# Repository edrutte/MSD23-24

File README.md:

# MSD 23-24 18661 Autonomous Chess Board
## Team Members

* [Evan Ruttenberg](https://github.com/edrutte) - System Engineer
* [Alec Paul](https://github.com/asp6244) - Project Manager
* Nick Larrabee - Purchasing Agent
* Devin Alberto - Facilitator
* [Justin Chienyuen](https://github.com/jcc3249) - Team Communicator

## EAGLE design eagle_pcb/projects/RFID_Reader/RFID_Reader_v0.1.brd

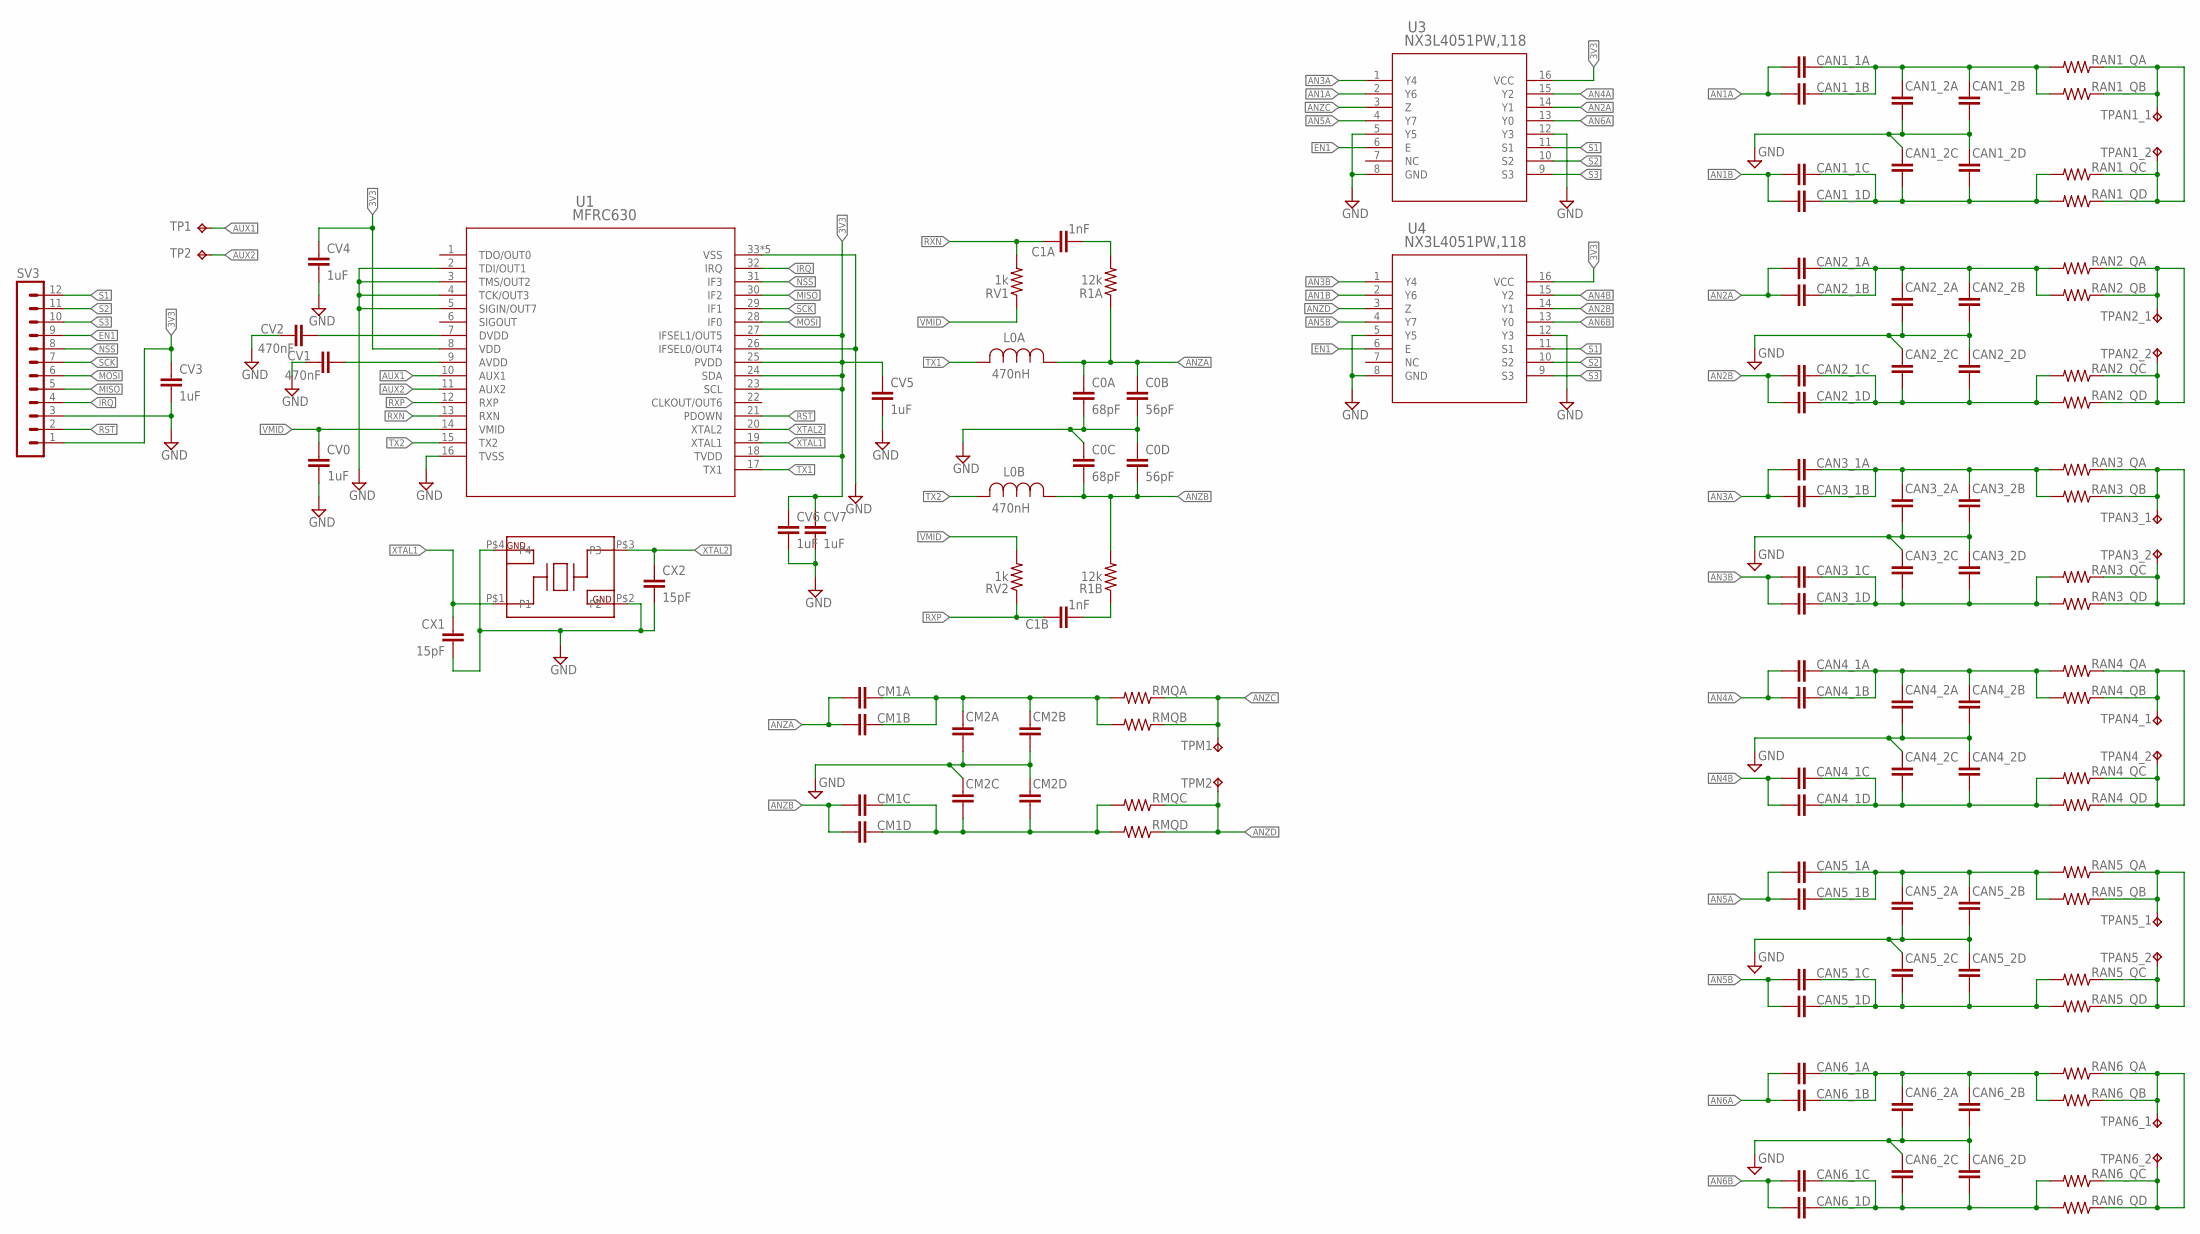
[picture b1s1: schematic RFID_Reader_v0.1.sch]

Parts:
C0A, C0C: 68pF; C0805
C0B, C0D: 56pF; C0805
C1A, C1B: 1nF; C0805
CAN1_1A, CAN1_1B, CAN1_1C, CAN1_1D, CAN1_2A, CAN1_2B, CAN1_2C, CAN1_2D, CAN2_1A, CAN2_1B, CAN2_1C, CAN2_1D, CAN2_2A, CAN2_2B, CAN2_2C, CAN2_2D, CAN3_1A, CAN3_1B, CAN3_1C, CAN3_1D, CAN3_2A, CAN3_2B, CAN3_2C, CAN3_2D, CAN4_1A, CAN4_1B, CAN4_1C, CAN4_1D, CAN4_2A, CAN4_2B, CAN4_2C, CAN4_2D, CAN5_1A, CAN5_1B, CAN5_1C, CAN5_1D, CAN5_2A, CAN5_2B, CAN5_2C, CAN5_2D, CAN6_1A, CAN6_1B, CAN6_1C, CAN6_1D, CAN6_2A, CAN6_2B, CAN6_2C, CAN6_2D: C-EUC0805; C0805
CM1A, CM1B, CM1C, CM1D, CM2A, CM2B, CM2C, CM2D: C-EUC0805; C0805
CV0, CV3, CV4, CV5, CV6, CV7: 1uF; C0402
CV1, CV2: 470nF; C0402
CX1, CX2: 15pF; C0402
L0A, L0B: 470nH; IND_BOURNS_CE201210_C
R1A, R1B: 12k; R0805
RAN1_QA, RAN1_QB, RAN1_QC, RAN1_QD, RAN2_QA, RAN2_QB, RAN2_QC, RAN2_QD, RAN3_QA, RAN3_QB, RAN3_QC, RAN3_QD, RAN4_QA, RAN4_QB, RAN4_QC, RAN4_QD, RAN5_QA, RAN5_QB, RAN5_QC, RAN5_QD, RAN6_QA, RAN6_QB, RAN6_QC, RAN6_QD: R-US_R0805; R0805
RMQA: R-US_R0805; R0805
RMQB: R-US_R0805; R0805
RMQC: R-US_R0805; R0805
RMQD: R-US_R0805; R0805
RV1, RV2: 1k; R0805
SV3: MA12-1
TP1, TP2: TPTP10R; TP10R
TPAN1_1, TPAN1_2, TPAN2_1, TPAN2_2, TPAN3_1, TPAN3_2, TPAN4_1, TPAN4_2, TPAN5_1, TPAN5_2, TPAN6_1, TPAN6_2: TPTP10R; TP10R
TPM1, TPM2: TPTP10R; TP10R
U1: MFRC630; HVQFN32_SOT617-1_NXP-M
U2: E3SB27; DFN320X250X75-4N
U3, U4: NX3L4051PW,118; TSSOP16_NXP-M

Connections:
3V3: CV3.1, CV4.1, CV5.1, CV6.1, CV7.1, SV3.1, U1.8 (VDD), U1.18 (TVDD), U1.23 (SCL), U1.24 (SDA), U1.25 (PVDD), U1.27 (IFSEL1/OUT5), U3.16 (VCC), U4.16 (VCC)
AN1A: CAN1_1A.2, CAN1_1B.2, U3.2 (Y6)
AN1B: CAN1_1C.2, CAN1_1D.2, U4.2 (Y6)
AN2A: CAN2_1A.2, CAN2_1B.2, U3.14 (Y1)
AN2B: CAN2_1C.2, CAN2_1D.2, U4.14 (Y1)
AN3A: CAN3_1A.2, CAN3_1B.2, U3.1 (Y4)
AN3B: CAN3_1C.2, CAN3_1D.2, U4.1 (Y4)
AN4A: CAN4_1A.2, CAN4_1B.2, U3.15 (Y2)
AN4B: CAN4_1C.2, CAN4_1D.2, U4.15 (Y2)
AN5A: CAN5_1A.2, CAN5_1B.2, U3.4 (Y7)
AN5B: CAN5_1C.2, CAN5_1D.2, U4.4 (Y7)
AN6A: CAN6_1A.2, CAN6_1B.2, U3.13 (Y0)
AN6B: CAN6_1C.2, CAN6_1D.2, U4.13 (Y0)
ANZA: C0A.1, C0B.1, CM1A.2, CM1B.2, L0A.1, R1A.1
ANZB: C0C.2, C0D.2, CM1C.2, CM1D.2, L0B.1, R1B.2
ANZC: RMQA.1, RMQB.1, TPM1.TP, U3.3 (Z)
ANZD: RMQC.1, RMQD.1, TPM2.TP, U4.3 (Z)
AUX1: TP1.TP, U1.10 (AUX1)
AUX2: TP2.TP, U1.11 (AUX2)
EN1: SV3.9, U3.6 (E), U4.6 (E)
GND: C0A.2, C0B.2, C0C.1, C0D.1, CAN1_2A.2, CAN1_2B.2, CAN1_2C.1, CAN1_2D.1, CAN2_2A.2, CAN2_2B.2, CAN2_2C.1, CAN2_2D.1, CAN3_2A.2, CAN3_2B.2, CAN3_2C.1, CAN3_2D.1, CAN4_2A.2, CAN4_2B.2, CAN4_2C.1, CAN4_2D.1, CAN5_2A.2, CAN5_2B.2, CAN5_2C.1, CAN5_2D.1, CAN6_2A.2, CAN6_2B.2, CAN6_2C.1, CAN6_2D.1, CM2A.2, CM2B.2, CM2C.1, CM2D.1, CV0.2, CV1.2, CV2.2, CV3.2, CV4.2, CV5.2, CV6.2, CV7.2, CX1.2, CX2.2, SV3.3, U1.2 (TDI/OUT1), U1.3 (TMS/OUT2), U1.4 (TCK/OUT3), U1.5 (SIGIN/OUT7), U1.16 (TVSS), U1.26 (IFSEL0/OUT4), U1.33 (VSS), U1.P$1 (VSS), U1.P$2 (VSS), U1.P$3 (VSS), U1.P$4 (VSS), U2.P$2 (P2), U2.P$4 (P4), U3.5 (Y5), U3.8 (GND), U3.12 (Y3), U4.5 (Y5), U4.8 (GND), U4.12 (Y3)
IRQ: SV3.4, U1.32 (IRQ)
MISO: SV3.5, U1.30 (IF2)
MOSI: SV3.6, U1.28 (IF0)
unnamed: CM1C.1, CM1D.1, CM2C.2, CM2D.2, RMQC.2, RMQD.2
unnamed: C1A.2, R1A.2
unnamed: CM1A.1, CM1B.1, CM2A.1, CM2B.1, RMQA.2, RMQB.2
unnamed: CAN2_1C.1, CAN2_1D.1, CAN2_2C.2, CAN2_2D.2, RAN2_QC.2, RAN2_QD.2
unnamed: CAN2_1A.1, CAN2_1B.1, CAN2_2A.1, CAN2_2B.1, RAN2_QA.2, RAN2_QB.2
unnamed: RAN2_QA.1, RAN2_QB.1, RAN2_QC.1, RAN2_QD.1, TPAN2_1.TP, TPAN2_2.TP
unnamed: CAN1_1C.1, CAN1_1D.1, CAN1_2C.2, CAN1_2D.2, RAN1_QC.2, RAN1_QD.2
unnamed: CAN1_1A.1, CAN1_1B.1, CAN1_2A.1, CAN1_2B.1, RAN1_QA.2, RAN1_QB.2
unnamed: RAN1_QA.1, RAN1_QB.1, RAN1_QC.1, RAN1_QD.1, TPAN1_1.TP, TPAN1_2.TP
unnamed: CAN3_1C.1, CAN3_1D.1, CAN3_2C.2, CAN3_2D.2, RAN3_QC.2, RAN3_QD.2
unnamed: CAN3_1A.1, CAN3_1B.1, CAN3_2A.1, CAN3_2B.1, RAN3_QA.2, RAN3_QB.2
unnamed: RAN3_QA.1, RAN3_QB.1, RAN3_QC.1, RAN3_QD.1, TPAN3_1.TP, TPAN3_2.TP
unnamed: CAN4_1C.1, CAN4_1D.1, CAN4_2C.2, CAN4_2D.2, RAN4_QC.2, RAN4_QD.2
unnamed: CAN4_1A.1, CAN4_1B.1, CAN4_2A.1, CAN4_2B.1, RAN4_QA.2, RAN4_QB.2
unnamed: RAN4_QA.1, RAN4_QB.1, RAN4_QC.1, RAN4_QD.1, TPAN4_1.TP, TPAN4_2.TP
unnamed: CAN5_1C.1, CAN5_1D.1, CAN5_2C.2, CAN5_2D.2, RAN5_QC.2, RAN5_QD.2
unnamed: CAN5_1A.1, CAN5_1B.1, CAN5_2A.1, CAN5_2B.1, RAN5_QA.2, RAN5_QB.2
unnamed: C1B.2, R1B.1
unnamed: RAN5_QA.1, RAN5_QB.1, RAN5_QC.1, RAN5_QD.1, TPAN5_1.TP, TPAN5_2.TP
unnamed: CAN6_1C.1, CAN6_1D.1, CAN6_2C.2, CAN6_2D.2, RAN6_QC.2, RAN6_QD.2
unnamed: CAN6_1A.1, CAN6_1B.1, CAN6_2A.1, CAN6_2B.1, RAN6_QA.2, RAN6_QB.2
unnamed: RAN6_QA.1, RAN6_QB.1, RAN6_QC.1, RAN6_QD.1, TPAN6_1.TP, TPAN6_2.TP
unnamed: CV2.1, U1.7 (DVDD)
unnamed: CV1.1, U1.9 (AVDD)
NSS: SV3.8, U1.31 (IF3)
RST: SV3.2, U1.21 (PDOWN)
RXN: C1A.1, RV1.2, U1.13 (RXN)
RXP: C1B.1, RV2.1, U1.12 (RXP)
S1: SV3.12, U3.11 (S1), U4.11 (S1)
S2: SV3.11, U3.10 (S2), U4.10 (S2)
S3: SV3.10, U3.9 (S3), U4.9 (S3)
SCK: SV3.7, U1.29 (IF1)
TX1: L0A.2, U1.17 (TX1)
TX2: L0B.2, U1.15 (TX2)
VMID: CV0.1, RV1.1, RV2.2, U1.14 (VMID)
XTAL1: CX1.1, U1.19 (XTAL1), U2.P$1 (P1)
XTAL2: CX2.1, U1.20 (XTAL2), U2.P$3 (P3)

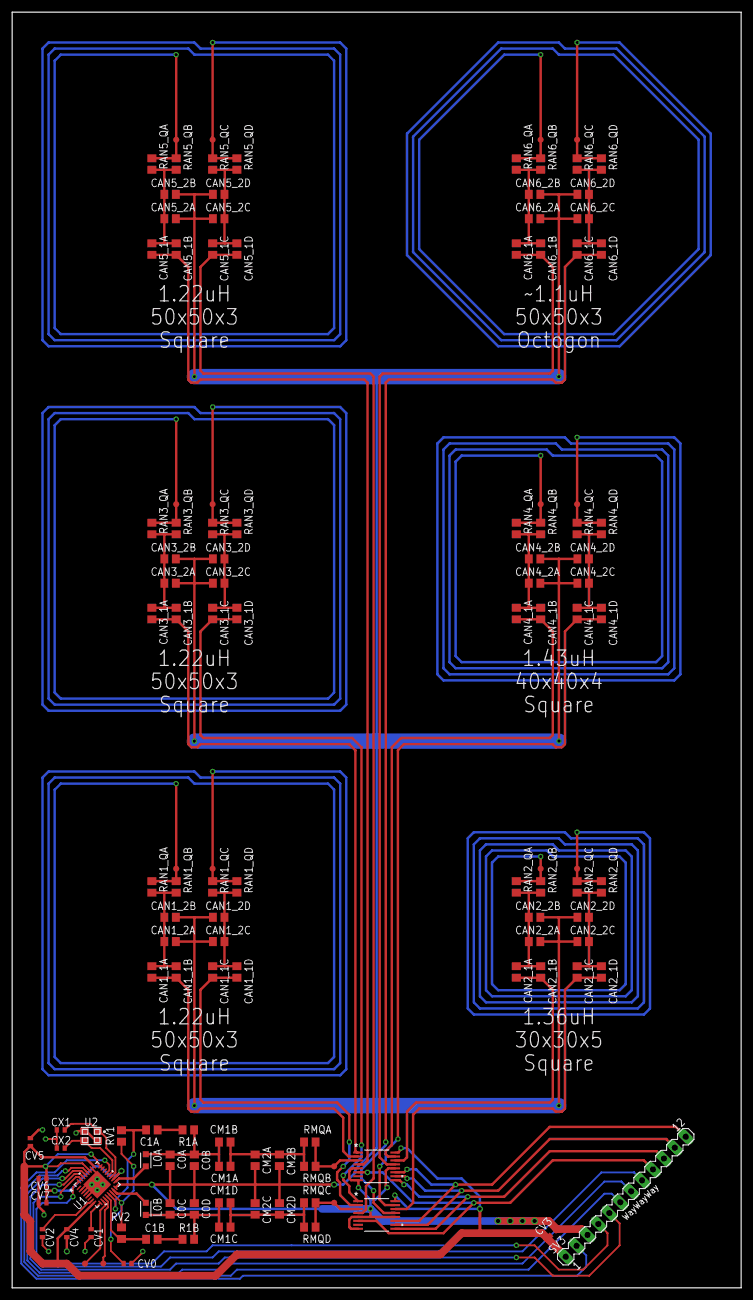
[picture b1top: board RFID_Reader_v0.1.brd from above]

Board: 2 copper layers, 120.0 x 210.0 mm, 127 parts (0 on the bottom side), 61 nets.

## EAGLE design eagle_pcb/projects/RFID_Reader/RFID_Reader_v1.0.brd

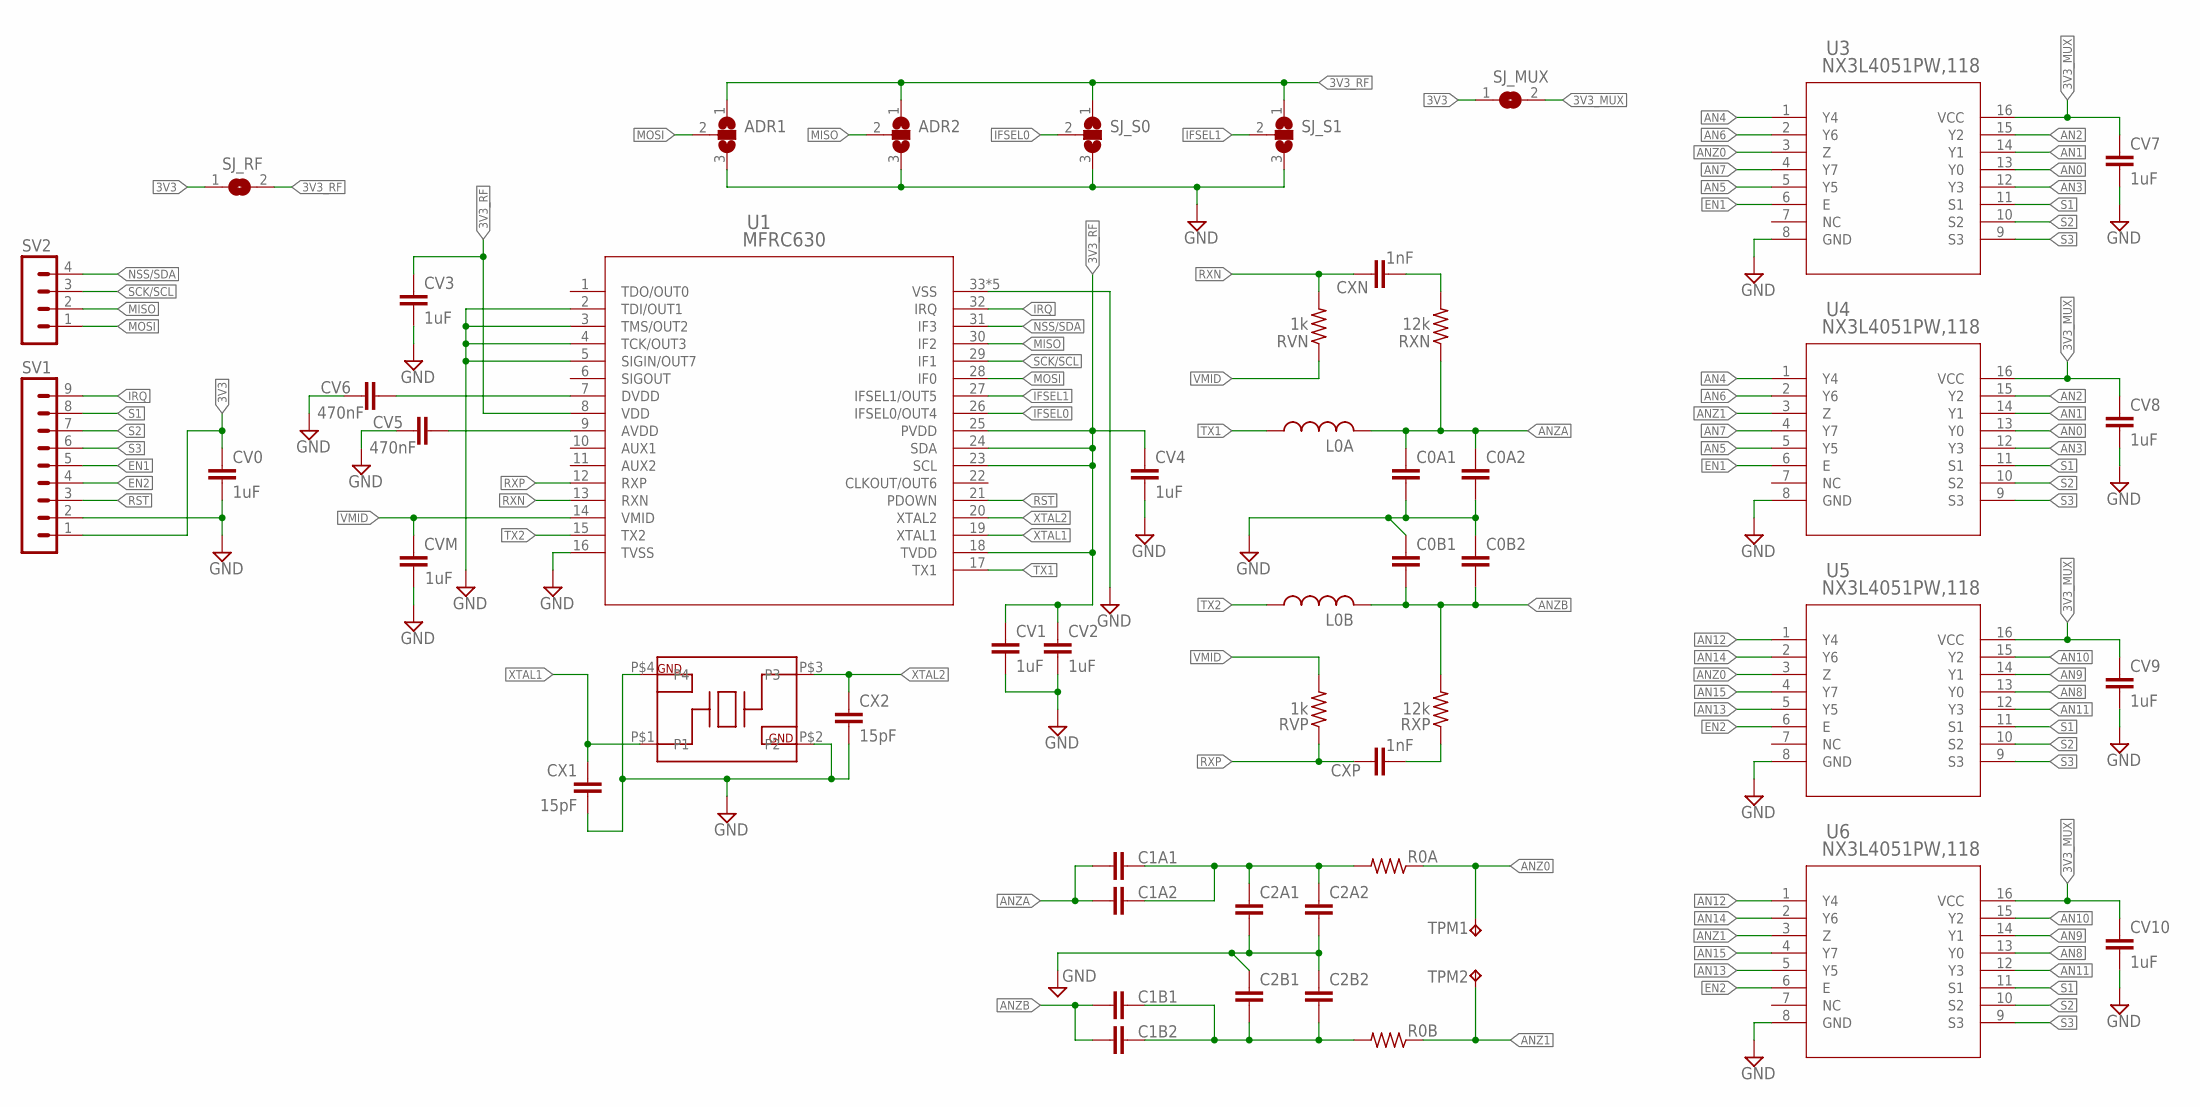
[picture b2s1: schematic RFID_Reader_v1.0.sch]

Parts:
ADR1, ADR2: SJ2W; SJ_2
C0A1, C0A2, C0B1, C0B2, C1A1, C1A2, C1B1, C1B2, C2A1, C2A2, C2B1, C2B2: C-EUC0805; C0805
CV0, CV1, CV2, CV3, CV4, CV7, CV8, CV9, CV10: 1uF; C0402
CV5, CV6: 470nF; C0402
CVM: 1uF; C0402
CX1, CX2: 15pF; C0402
CXN: 1nF; C0805
CXP: 1nF; C0805
L0A, L0B: L0806
R0A, R0B: R-US_R0805; R0805
RVN: 1k; R0805
RVP: 1k; R0805
RXN: 12k; R0805
RXP: 12k; R0805
SJ_MUX: SJ
SJ_RF: SJ
SJ_S0, SJ_S1: SJ2W; SJ_2
SV1: MA09-1
SV2: MA04-1
TPM1, TPM2: TPTP10R; TP10R
U1: MFRC630; HVQFN32_SOT617-1_NXP-M
U2: E3SB27; DFN320X250X75-4N
U3, U4, U5, U6: NX3L4051PW,118; TSSOP16_NXP-M

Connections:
3V3: CV0.1, SJ_MUX.1, SJ_RF.1, SV1.1
3V3_MUX: CV7.1, CV8.1, CV9.1, CV10.1, SJ_MUX.2, U3.16 (VCC), U4.16 (VCC), U5.16 (VCC), U6.16 (VCC)
3V3_RF: ADR1.1, ADR2.1, CV1.1, CV2.1, CV3.1, CV4.1, SJ_RF.2, SJ_S0.1, SJ_S1.1, U1.8 (VDD), U1.18 (TVDD), U1.23 (SCL), U1.24 (SDA), U1.25 (PVDD)
AN0: U3.13 (Y0), U4.13 (Y0)
AN1: U3.14 (Y1), U4.14 (Y1)
AN2: U3.15 (Y2), U4.15 (Y2)
AN3: U3.12 (Y3), U4.12 (Y3)
AN4: U3.1 (Y4), U4.1 (Y4)
AN5: U3.5 (Y5), U4.5 (Y5)
AN6: U3.2 (Y6), U4.2 (Y6)
AN7: U3.4 (Y7), U4.4 (Y7)
AN8: U5.13 (Y0), U6.13 (Y0)
AN9: U5.14 (Y1), U6.14 (Y1)
AN10: U5.15 (Y2), U6.15 (Y2)
AN11: U5.12 (Y3), U6.12 (Y3)
AN12: U5.1 (Y4), U6.1 (Y4)
AN13: U5.5 (Y5), U6.5 (Y5)
AN14: U5.2 (Y6), U6.2 (Y6)
AN15: U5.4 (Y7), U6.4 (Y7)
ANZ0: R0A.1, TPM1.TP, U3.3 (Z), U5.3 (Z)
ANZ1: R0B.1, TPM2.TP, U4.3 (Z), U6.3 (Z)
ANZA: C0A1.1, C0A2.1, C1A1.2, C1A2.2, L0A.2, RXN.1
ANZB: C0B1.2, C0B2.2, C1B1.2, C1B2.2, L0B.2, RXP.2
EN1: SV1.5, U3.6 (E), U4.6 (E)
EN2: SV1.4, U5.6 (E), U6.6 (E)
GND: ADR1.3, ADR2.3, C0A1.2, C0A2.2, C0B1.1, C0B2.1, C2A1.2, C2A2.2, C2B1.1, C2B2.1, CV0.2, CV1.2, CV2.2, CV3.2, CV4.2, CV5.2, CV6.2, CV7.2, CV8.2, CV9.2, CV10.2, CVM.2, CX1.2, CX2.2, SJ_S0.3, SJ_S1.3, SV1.2, U1.2 (TDI/OUT1), U1.3 (TMS/OUT2), U1.4 (TCK/OUT3), U1.5 (SIGIN/OUT7), U1.16 (TVSS), U1.33 (VSS), U1.P$1 (VSS), U1.P$2 (VSS), U1.P$3 (VSS), U1.P$4 (VSS), U2.P$2 (P2), U2.P$4 (P4), U3.8 (GND), U4.8 (GND), U5.8 (GND), U6.8 (GND)
IFSEL0: SJ_S0.2, U1.26 (IFSEL0/OUT4)
IFSEL1: SJ_S1.2, U1.27 (IFSEL1/OUT5)
IRQ: SV1.9, U1.32 (IRQ)
MISO: ADR2.2, SV2.2, U1.30 (IF2)
MOSI: ADR1.2, SV2.1, U1.28 (IF0)
unnamed: C1B1.1, C1B2.1, C2B1.2, C2B2.2, R0B.2
unnamed: CXN.2, RXN.2
unnamed: C1A1.1, C1A2.1, C2A1.1, C2A2.1, R0A.2
unnamed: CXP.2, RXP.1
unnamed: CV6.1, U1.7 (DVDD)
unnamed: CV5.1, U1.9 (AVDD)
NSS/SDA: SV2.4, U1.31 (IF3)
RST: SV1.3, U1.21 (PDOWN)
RXN: CXN.1, RVN.2, U1.13 (RXN)
RXP: CXP.1, RVP.1, U1.12 (RXP)
S1: SV1.8, U3.11 (S1), U4.11 (S1), U5.11 (S1), U6.11 (S1)
S2: SV1.7, U3.10 (S2), U4.10 (S2), U5.10 (S2), U6.10 (S2)
S3: SV1.6, U3.9 (S3), U4.9 (S3), U5.9 (S3), U6.9 (S3)
SCK/SCL: SV2.3, U1.29 (IF1)
TX1: L0A.1, U1.17 (TX1)
TX2: L0B.1, U1.15 (TX2)
VMID: CVM.1, RVN.1, RVP.2, U1.14 (VMID)
XTAL1: CX1.1, U1.19 (XTAL1), U2.P$1 (P1)
XTAL2: CX2.1, U1.20 (XTAL2), U2.P$3 (P3)

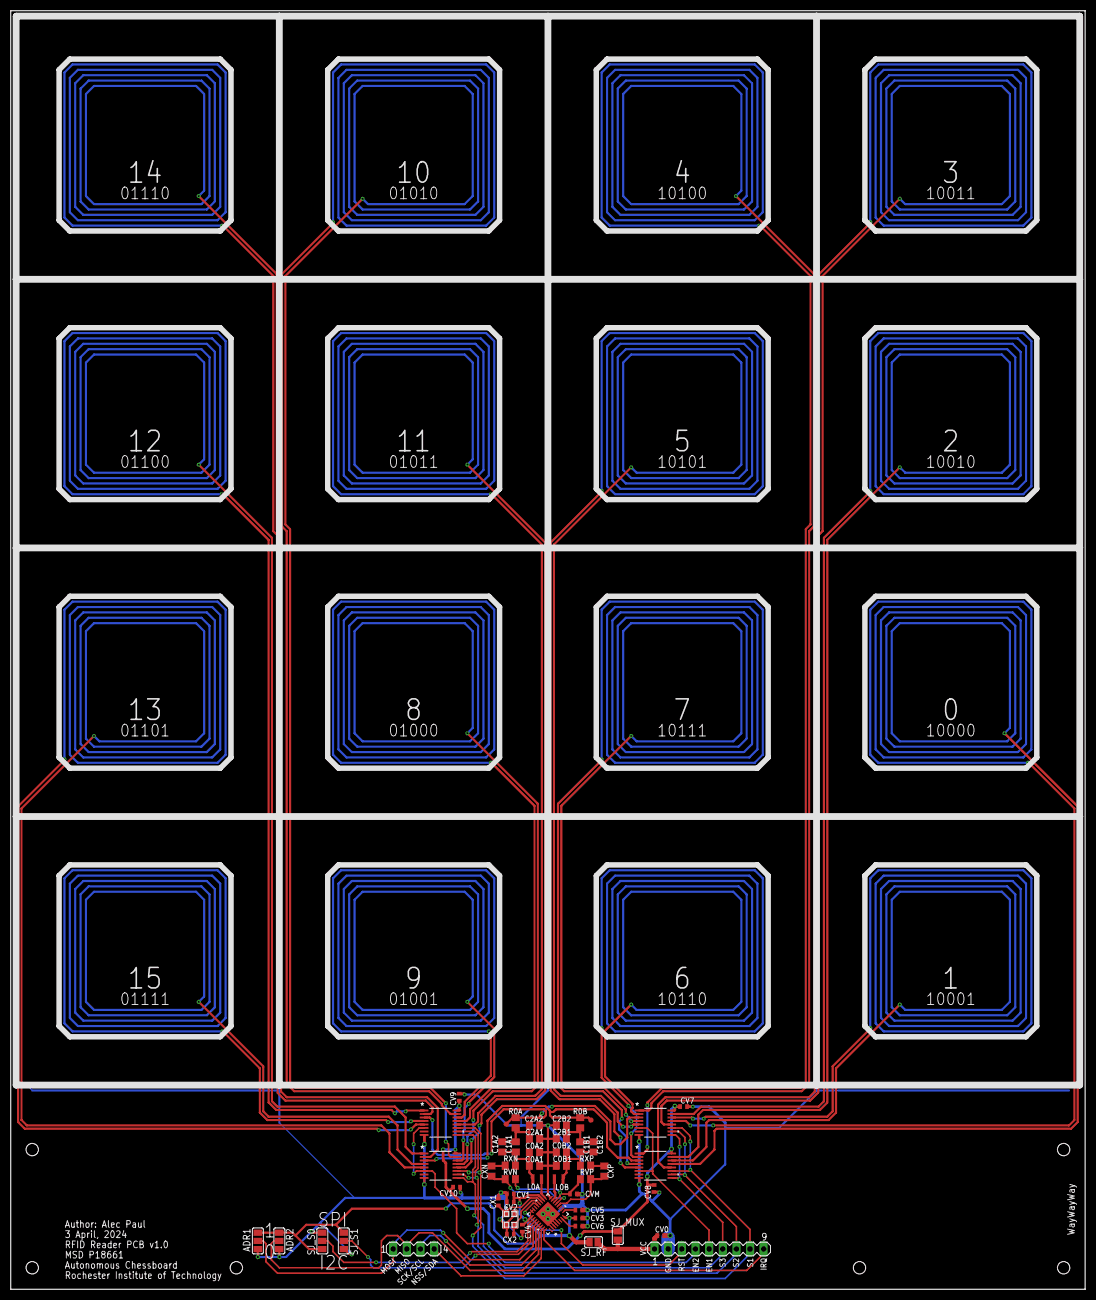
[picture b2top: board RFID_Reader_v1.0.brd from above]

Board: 2 copper layers, 200.0 x 238.0 mm, 52 parts (0 on the bottom side), 50 nets.

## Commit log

2023-11-07 Add README
2023-11-07 Add github profiles
2023-11-07 Add Stockfish as submodule
2023-11-07 Add LICENSE.md
2023-11-07 Add profile link for Justin
2023-11-15 Setup CMake build
2023-11-16 Add README for building project
2023-11-30 Keep CMake chaff out of Stockfish submodule
2023-11-30 Use native arch by default
2023-11-30 Don't try to install Stockfish
2024-01-02 Ignore JetBrains project files
2024-01-18 Update Stockfish to 6c02329 for native arch detection
2024-01-22 PoC for stockfish uci communication
2024-01-25 Refine Stockfish IPC
2024-01-31 Simplify Stockfish stdout read
2024-02-07 Verify Stockfish response and initialize Pi 5 gpio
2024-02-11 Rename CMake project to match include guards
2024-02-12 Set some engine options, use epoll to wait for stockfish response.
2024-02-12 Close gpio chip
2024-02-14 Initial work for SPI
2024-02-20 Add patch to suppress stockfish info messages
2024-02-26 Update Stockfish to release 16.1 and refresh patch
2024-02-26 Update CMake ExternalProject for Stockfish
2024-02-26 Create macros to print number of bytes read and written.
2024-02-26 Gate gpio behind check for Pi 5 architecture
2024-02-28 Make fish out pipe O_NONBLOCK too. Handle epoll timeout.
2024-03-04 Use wiringPi instead of libgpiod
2024-03-25 Only try to link WiringPi on arm
2024-03-25 Implement i2c for Pi
2024-03-25 Move includes not used in prototypes out of SPI header
2024-03-27 Initial stepper movement
2024-03-27 Initial rfid access
2024-03-27 Fix typo and remove old libgpio code
2024-03-27 Add rfid smoke test
2024-04-01 Initialize all fields of spi_ioc_transfer
2024-04-01 Initialize wiringPi and stub functions on non-pi platforms
2024-04-03 Take microstepping into account
2024-04-03 Initial commit for lcd
2024-04-07 initial stockfish interface commit
2024-04-07 implemented end of game detection
2024-04-07 cleaned up some code
2024-04-10 Stockfish commands should end with a newline. The use of O_NONBLOCK pipes seems to be the reason this manifested as a bizarre crash rather than a hang.
2024-04-15 Port Adafruit MFRC630 library to Raspberry Pi and replace previous library
2024-04-15 Git couldn't fathom modifying and renaming a file at once
2024-04-17 Suppress printing NNUE info
2024-04-17 Start implementing chess infrastructure
2024-04-17 Pass fd to init_rfid instead of opening itself
2024-04-22 Clang-tidy and typo lint Adafruit code
2024-04-22 Add initial motor code from Justin
2024-04-22 Suppress more Stockfish info
2024-04-22 Continue chess infrastructure
2024-04-23 Working on RFID
2024-04-24 Add rfid function prototypes
2024-04-24 added validate_move()
2024-04-24 Add prototype and stub for movement function
2024-04-24 Add chess-library for validating moves
2024-04-25 Got all 3 boards working with old code
2024-04-25 finished cleaning up the functions for rfid
2024-04-25 Properly add chess-library submodule
2024-04-25 pi_rfid.h needs to be extern "C"
2024-04-25 Call init_chess
2024-04-25 Cherry-pick simplified game over check from Alec
2024-04-25 Add missing enum keyword
2024-04-25 Implement capture detection
2024-04-26 Call movePiece twice for en passant and castling
2024-04-26 LCD take 2, using a library this time
2024-04-26 Fix some accidentally hard-coded pins
2024-04-26 Reallocate stepper pins
2024-04-26 Correct i2c adapter
2024-04-29 final branch commit
2024-04-29 final main commit
2024-04-29 Added RFID PCB stuff
2024-04-30 final push

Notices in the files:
parts and their libraries:
COPYRIGHT: Copyright (C) 2024 Ultra Librarian. All rights reserved.
